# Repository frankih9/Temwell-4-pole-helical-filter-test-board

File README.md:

# Temwell-7H-4-pole-helical-filter-test-board
Kicad files for Temwell 7H 4-pole series evaluation PCB.  
This test board was never built.  
http://www.temwell.com/products.php?id=66

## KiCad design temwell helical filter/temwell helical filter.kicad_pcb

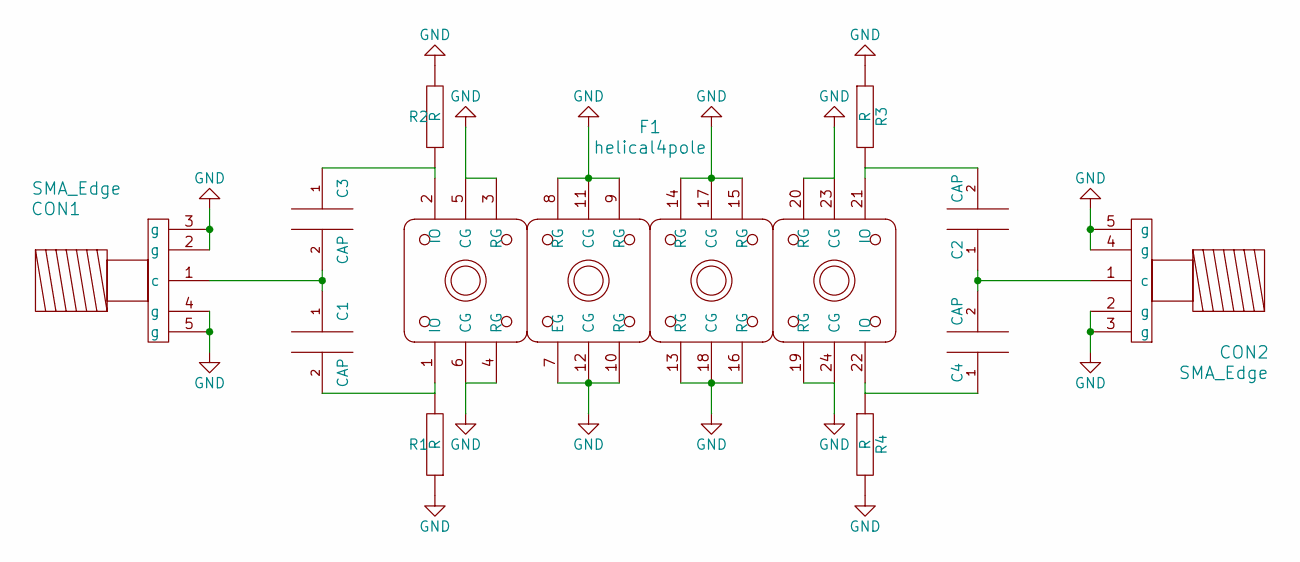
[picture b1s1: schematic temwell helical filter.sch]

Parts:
C1, C2, C3, C4: CAP; C_0402_NoSilk
CON1, CON2: SMA_Edge
F1: helical4pole; helical4p
R1, R2, R3, R4: R; R_0402_NoSilk

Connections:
GND: CON1.2 (g), CON1.3 (g), CON1.4 (g), CON1.5 (g), CON2.2 (g), CON2.3 (g), CON2.4 (g), CON2.5 (g), F1.3 (RG), F1.4 (RG), F1.5 (CG), F1.6 (CG), F1.7 (EG), F1.8 (RG), F1.9 (RG), F1.10 (RG), F1.11 (CG), F1.12 (CG), F1.13 (RG), F1.14 (RG), F1.15 (RG), F1.16 (RG), F1.17 (CG), F1.18 (CG), F1.19 (RG), F1.20 (RG), F1.23 (CG), F1.24 (CG), R1.1, R2.2, R3.1, R4.2
unnamed: C1.1, C3.2, CON1.1 (c)
unnamed: C1.2, F1.1 (IO), R1.2
unnamed: C2.1, C4.2, CON2.1 (c)
unnamed: C2.2, F1.21 (IO), R3.2
unnamed: C3.1, F1.2 (IO), R2.1
unnamed: C4.1, F1.22 (IO), R4.1

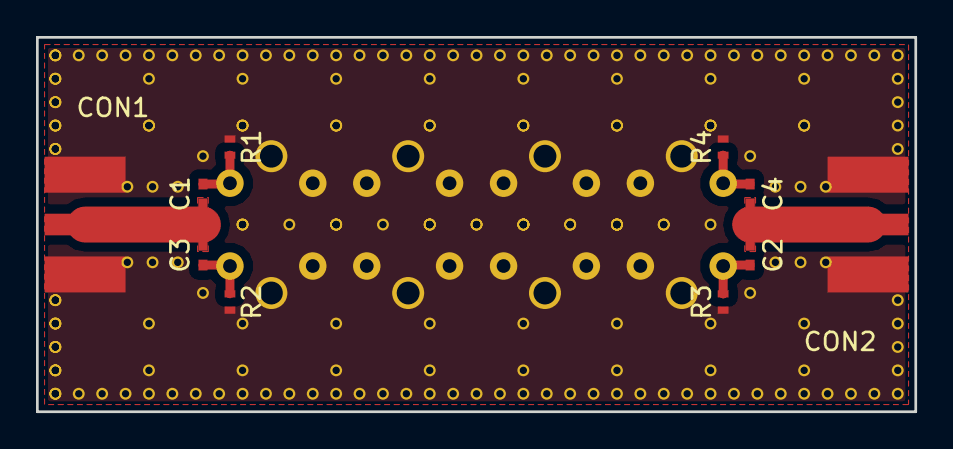
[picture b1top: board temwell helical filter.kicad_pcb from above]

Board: 2 copper layers, 48.8 x 20.8 mm, 11 parts (1 on the bottom side), 7 nets.
